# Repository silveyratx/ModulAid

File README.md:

# Modulaid

### Overview
ModulAid was born at UT Austin as a Senior Design Project for 5 Electrical Engineering [students](#contributors). Their senior design class was a special section called "Startup Senior Design" and the students thought up their own project rather than doing an industry or faculty sponsored project.

ModulAid extends a smartphone by providing an easy to use interface for many different types of sensors. The main hub plugs into the smartphone via the headphone jack. Through the connection with the headphone jack, the board is able to communicate with the iOS app as well as harvest power. Sensors can then be attached to the shared sensor board. The board acquires data from the sensors, transmits it to the smartphone, and from there it is displayed to the user.

The team chose to focus on making ModulAid a system for medical devices. The ModulAid app was designed to make access to health information very cheap. The team wanted to make it as easy as possible for people to get insights about their own health and the health in their communities.

### Hardware
Our initial development was done on the NXP Quick-Jack development kit. Then we designed a 2.4 x 1.45 inch PCB, shown below. The Quick-Jack acted as our reference design but with unnecessary components removed and additional components added to satisfy design requirements.

Connecting the board with the phone is as simple as plugging it into the headphone jack. All communication with the phone is done through the four-terminal headphone jack. The four pins in the headphone jack are left audio, right audio, microphone, and ground.

The right audio channel is dedicated to transferring power through a constant audio wave. The signal is fed into a voltage rectifier that converts the low voltage AC signal into a higher voltage DC signal. The DC voltage is fed into a 3.3V regulator that produces a constant voltage for the microcontroller and sensors. The max power that can be harvested from the phone is about 15mW, but the exact value varies from phone to phone. The board also has a CR2032 battery on the back. When additional current is needed for a sensor, it can be drawn from the battery.

Besides providing power to the sensors, the board must be able to communicate with them. We created our own sensor interface so that all our sensors connect through the same port. All our compatible sensors fall into two categories, either those that produce an analog voltage signal or those that communicate through a peripheral on the microcontroller. We added a 2 channel 10-bit ADC (MCP3002) and a dual SPDT (single pole double throw) analog switch (TS3A24157). The signal lines from the sensor port connect to the common inputs of the SPDT switch. The firmware controls the input to the switch to either connect the sensor signals to the ADC or directly to the microcontroller. The schematic is included in the Hardware directory.

### Firmware
The firmware runs on the microcontroller(NXP LPC812) of the ModulAid board. The purpose of the firmware is to create a channel of communication between the smartphone and the various sensors. The firmware receives commands from the smartphone, initializes the hardware, acquires data, and sends the data to the smartphone. Upon reset of the device, the firmware performs the needed initialization for the device, then waits to receive a command from the phone. The command tells the firmware which sensor the user has selected. This is necessary because each sensor communicates with the board differently and requires a unique initialization. For example, the board uses I2C (Inter-Integrated Circuit) to communicate with the IR thermometer, but reads a voltage through the ADC (Analog to Digital Converter) with SPI (Serial Peripheral Interface) for the pulse sensor.

To use the ADC, first we must set the input to the dual SPDT switch such that the sensor wires connect to the inputs of the ADC. We then can sample the ADC by sending a command through SPI to the ADC. The command wakes up the ADC from its sleep state. From there it samples the requested input channel and sends the 10 bit result back. For some sensors, the raw ADC value might be a meaningful piece of data, but in the case of the pulse sensor we must take periodic readings that can be processed into a heart rate in beats per minute (BPM). The pulse sensor readings create a pulse wave. We calculate the BPM by measuring the time between peaks of the waves. The firmware keeps a running average of the BPM and when requested send the value to the smartphone.

For all sensors that don’t make use of the ADC, the input to the dual SPDT switch is set such that the signals from the sensor connect directly to the pins of the microcontroller. The microcontroller, the NXP LPC812, has an internal switch matrix that allows the hardware peripherals to be connected to almost any chosen pin. Because of this switch matrix, we can use the same set of pins for various communication protocols. When the IR thermometer is connected, the firmware assigns the I2C function to the sensor pins. Through the I2C bus, we can poll the thermometer for its most recent temperature reading.

The current hardware revision supports sensors that output an analog voltage or communicate through I2C or UART. SPI could be used for sensor communication if one more signal line was added between the microcontroller and the sensor port.

### iOS Application
The application user interface is the main “face” of the product for a user. Our goal in designing the user interface was to make the application so easy to use that it required no instruction. To accomplish this goal, we decided to use pictures rather than words whenever possible. This way, people of different cultures could use the same version of the app. Screenshots of are included below.

The user interface has three views that carry out the main functions of the application. There is a Home view, a Heatmap view, and a History. The Home view is where the user goes to take a measurement. From the Home view initial screen, the user selects which type of measurement they want to take. After the user selects their device, they are guided by a series of visual prompts to take the reading. In Heatmap view, the user can see what other ModulAid activity is happening around them. The Heatmap shows the locations and relative temperatures of other users. The heatmap is one example of real time health analytics that ModulAid offers, and in the future, it could be used to analyze the health in communities. In History view, a user can see the recent sensor measurements that were taken locally on their personal device.

All collected data is stored anonymously to a FireBase database. Along with the data point we store the location. Further insights and analytics could be generated from this data. The heatmap is one example of this, providing a way to plot the location and severity of fever on a map.

### Demo
Here is a short video demonstrating the functionality: https://vimeo.com/168209562

### Going Forward
Due to the project’s scope in the Senior Design class, ModulAid only supports two sensors, a thermometer, and a heart rate monitor. There are many ways the project could move forward:      
	-Add support for additional sensors     
	-Create user accounts to give more specialized health insights      
	-Create an Android app similiar to the iOS app       
	-Rework the firmware to deal with sensors in a more generic way, allowing new sensors to be added without updating the firmware.    
-and probably many more..

We created this GitHub Repository to document our project and let it live on through the internet. We hope someone out there finds it useful, helpful or even inspiring. Furthermore, the platform is not limited to medical sensors and could be a base for interfacing all sorts of sensors with a smartphone.

### Resources
ModulAid draws from several projects and frameworks:

NXP QuickJack: http://www.nxp.com/products/microcontrollers-and-processors/arm-processors/lpc-cortex-m-mcus/lpc-cortex-m0-plus-m0-mcus/lpc800-low-cost-cortex-m0-plus-mcus/om13069-smartphone-quick-jack-solution:OM13069

LFHeatMap: https://github.com/gpolak/LFHeatMap

Firebase: https://www.firebase.com/

### Contributors
Alex Lee, Cage Johnson, Sam Moser, Alejandro Silveyra, and Ammar Hazim (in order of appearance)    
Photo of team at UT Austin Electrical and Computer Engineering Senior Design Open House - Spring 2016

We would also like to thank our faculty mentor, Ramesh Yerraballi, for his support through out the project.

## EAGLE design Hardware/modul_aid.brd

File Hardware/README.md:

# ModulAid Hardware

Schematic and PCB created in EagleCAD

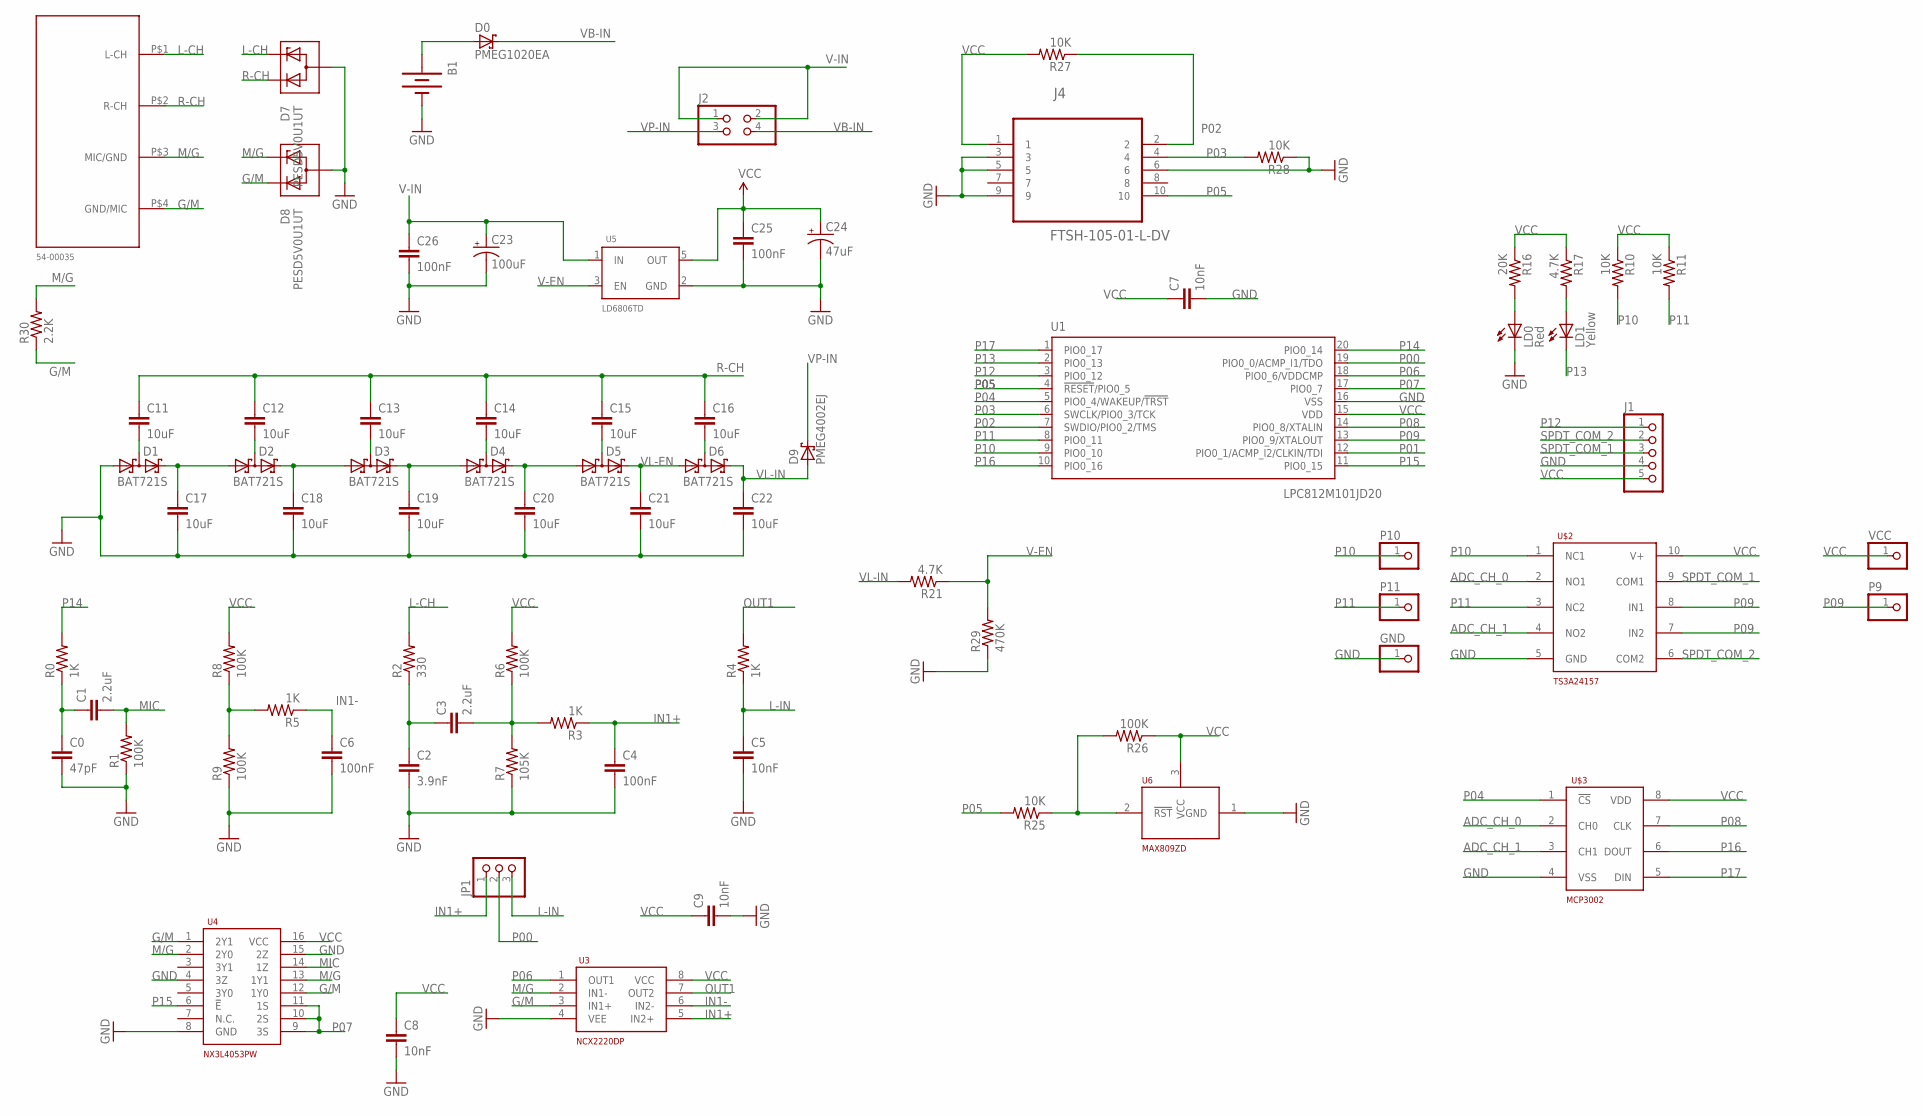
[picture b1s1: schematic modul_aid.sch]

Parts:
B1: BATTERY20PTH; BATTCOM_20MM_PTH
C0: 47pF; 0805-CAP
C1, C3: 2.2uF; 0805-CAP
C2: 3.9nF; 0805-CAP
C4, C6: 100nF; 0805-CAP
C5, C8, C9: 10nF; 0805-CAP
C7: 10nF; 0805
C11, C12, C13, C14, C15, C16, C17, C18, C19, C20, C21, C22: 10uF; 0805-CAP
C23: 100uF; EIA3216-KIT
C24: 47uF; EIA3216-KIT
C25, C26: 100nF; 0805
D0: PMEG1020EA; SOD323(F)
D1, D2, D3, D4, D5, D6: BAT721S; SOT23
D7, D8: PESD5V0U1UT; SOT23
D9: PMEG4002EJ; SOD323(F)
GND: PINHD-1X1; 1X01
J1: PINHD-1X5; 1X05
J2: PINHD-2X2; 2X02
J4: FTSH-105-01-L-DV; SAMTEC_FTSH-105-01-L-DV
JP1: PINHD-1X3; 1X03
LD0: Red; SML0805
LD1: Yellow; SML0805
P9, P10, P11: PINHD-1X1; 1X01
R0, R3, R4, R5: 1K; 0805
R1, R6, R8, R9, R26: 100K; 0805
R2: 330; 0805
R7: 105K; 0805
R10, R11, R25, R27, R28: 10K; 0805
R16: 20K; 0805
R17, R21: 4.7K; 0805
R29: 470K; 0805
R30: 2.2K; 0805
U1: LPC812M101JD20; SOT163-1
U3: NCX2220DP; SOT505-2
U4: NX3L4053PW; S0T403-1
U5: LD6806TD; SOT753
U6: MAX809ZD; SOT23-3
U$2: TS3A24157; VSSOP-10
U$3: MCP3002; SOIC8
U$4: TENSILITY54-00035; EE464SAUDIOJACK
VCC: PINHD-1X1; 1X01

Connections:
ADC_CH_0: U$2.2 (NO1), U$3.2 (CH0)
ADC_CH_1: U$2.4 (NO2), U$3.3 (CH1)
G/M: D8.2 (KD), R30.1, U3.3 (IN1+), U4.1 (2Y1), U4.12 (1Y0), U$4.P$4 (GND/MIC)
GND: B1.2 (-), C0.2, C2.2, C4.2, C5.2, C6.2, C7.2, C8.2, C9.2, C17.2, C18.2, C19.2, C20.2, C21.2, C22.2, C23.C (-), C24.C (-), C25.2, C26.2, D1.1 (A1), D7.3 (CA), D8.3 (CA), GND.1, J1.4, J4.3, J4.5, J4.6, J4.9, LD0.C, R1.1, R7.1, R9.1, R28.1, R29.1, U1.16 (VSS), U3.4 (VEE), U4.4 (3Z), U4.8 (GND), U4.15 (2Z), U5.2 (GND), U6.1 (GND), U$2.5 (GND), U$3.4 (VSS)
IN1+: C4.1, JP1.1, R3.1, U3.5 (IN2+)
IN1-: C6.1, R5.1, U3.6 (IN2-)
L-CH: D7.1 (KESD), R2.2, U$4.P$1 (L-CH)
L-IN: C5.1, JP1.3, R4.1
M/G: D8.1 (KESD), R30.2, U3.2 (IN1-), U4.2 (2Y0), U4.13 (1Y1), U$4.P$3 (MIC/GND)
MIC: C1.2, R1.2, U4.14 (1Z)
unnamed: C11.2, D1.3 (K1A2)
unnamed: C12.2, D2.3 (K1A2)
unnamed: C13.2, D3.3 (K1A2)
unnamed: C14.2, D4.3 (K1A2)
unnamed: C15.2, D5.3 (K1A2)
unnamed: C16.2, D6.3 (K1A2)
unnamed: B1.1 (+), D0.2 (A)
unnamed: C0.1, C1.1, R0.1
unnamed: C17.1, D1.2 (K2), D2.1 (A1)
unnamed: C18.1, D2.2 (K2), D3.1 (A1)
unnamed: C19.1, D3.2 (K2), D4.1 (A1)
unnamed: C20.1, D4.2 (K2), D5.1 (A1)
unnamed: R5.2, R8.1, R9.2
unnamed: C2.1, C3.1, R2.1
unnamed: R25.1, R26.2, U6.2 (!RST)
unnamed: C3.2, R3.2, R6.1, R7.2
unnamed: LD0.A, R16.2
unnamed: LD1.A, R17.2
OUT1: R4.2, U3.7 (OUT2)
P00: JP1.2, U1.19 (PIO0_0/ACMP_I1/TDO)
P01: U1.12 (PIO0_1/ACMP_I2/CLKIN/TDI)
P02: J4.2, R27.1, U1.7 (SWDIO/PIO0_2/TMS)
P03: J4.4, R28.2, U1.6 (SWCLK/PIO0_3/TCK)
P04: U1.5 (PIO0_4/WAKEUP/!TRST!), U$3.1 (!CS)
P05: J4.10, R25.2, U1.4 (!RESET!/PIO0_5)
P06: U1.18 (PIO0_6/VDDCMP), U3.1 (OUT1)
P07: U1.17 (PIO0_7), U4.9 (3S), U4.10 (2S), U4.11 (1S)
P08: U1.14 (PIO0_8/XTALIN), U$3.7 (CLK)
P09: P9.1, U1.13 (PIO0_9/XTALOUT), U$2.7 (IN2), U$2.8 (IN1)
P10: P10.1, R10.2, U1.9 (PIO0_10), U$2.1 (NC1)
P11: P11.1, R11.2, U1.8 (PIO0_11), U$2.3 (NC2)
P12: J1.1, U1.3 (PIO0_12)
P13: LD1.C, U1.2 (PIO0_13)
P14: R0.2, U1.20 (PIO0_14)
P15: U1.11 (PIO0_15), U4.6 (!E)
P16: U1.10 (PIO0_16), U$3.6 (DOUT)
P17: U1.1 (PIO0_17), U$3.5 (DIN)
R-CH: C11.1, C12.1, C13.1, C14.1, C15.1, C16.1, D7.2 (KD), U$4.P$2 (R-CH)
SPDT_COM_1: J1.3, U$2.9 (COM1)
SPDT_COM_2: J1.2, U$2.6 (COM2)
V-EN: R21.1, R29.2, U5.3 (EN)
V-IN: C23.A (+), C26.1, J2.1, J2.2, U5.1 (IN)
VB-IN: D0.1 (K), J2.4
VCC: C7.1, C8.1, C9.1, C24.A (+), C25.1, J1.5, J4.1, R6.2, R8.2, R10.1, R11.1, R16.1, R17.1, R26.1, R27.2, U1.15 (VDD), U3.8 (VCC), U4.16 (VCC), U5.5 (OUT), U6.3 (VCC), U$2.10 (V+), U$3.8 (VDD), VCC.1
VL-EN: C21.1, D5.2 (K2), D6.1 (A1)
VL-IN: C22.1, D6.2 (K2), D9.2 (A), R21.2
VP-IN: D9.1 (K), J2.3

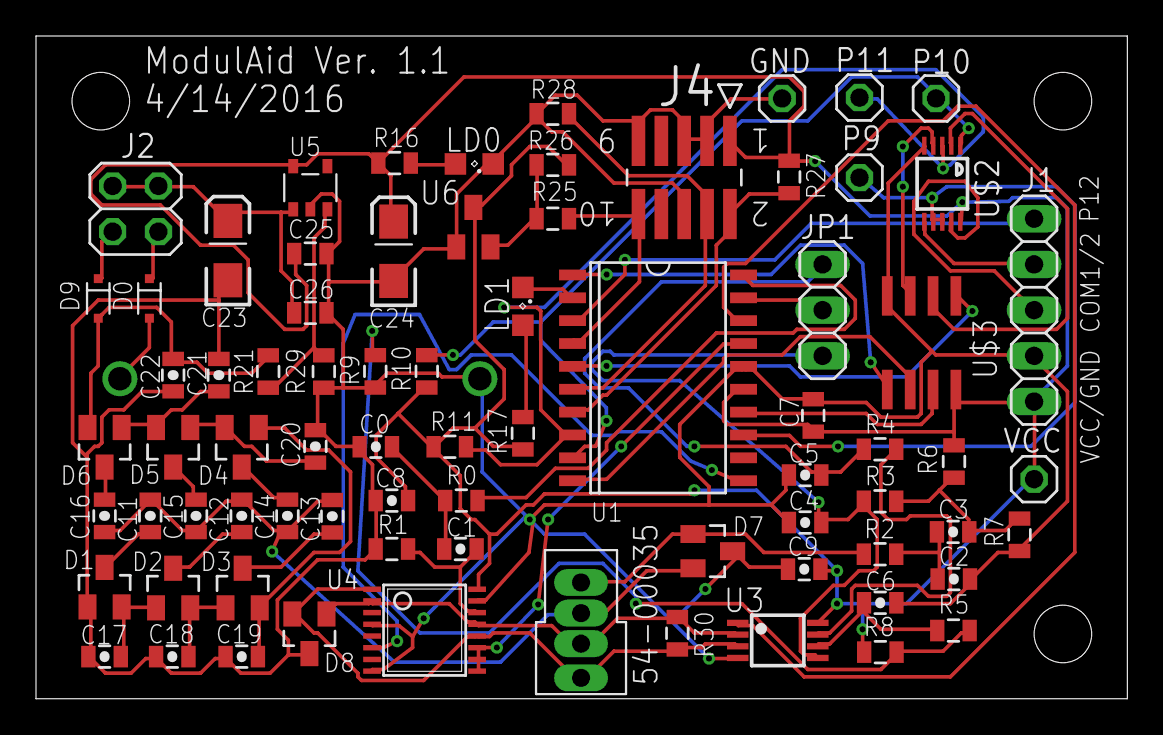
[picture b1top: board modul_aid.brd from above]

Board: 2 copper layers, 60.6 x 36.8 mm, 77 parts (1 on the bottom side), 56 nets.

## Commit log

2016-05-16 adds folders
2016-05-16 transfer to github
2016-05-16 syntax fixes
2016-05-16 line spacing fix
2016-05-16 adds images
2016-05-16 readme test
2016-05-17 iOS application
2016-05-17 cleared readme
2016-05-17 added schematic and pcb files
2016-05-17 adds ios images
2016-05-17 fix to images
2016-05-17 fix to image path
2016-05-17 iOS application, fixed ModulAid folder issue
2016-05-17 fixed iOS project after changing folder name from ModulAid to modulaidUI
2016-05-17 added readme for iOS app
2016-05-17 fixed iOS readme
2016-05-17 readme update
2016-05-17 path fix
2016-05-17 style fix
2016-05-17 photo description
2016-05-17 team name ordering change
2016-05-21 readme addiitions
2016-05-21 added heatmap screenshot
2016-05-21 smaller heatmap screenshot
2016-05-21 screenshot replaced with combo of all three screens
2016-05-21 copy fixes
2016-05-21 added hardware and firmware sections
2016-05-21 created an iOS section
2016-05-21 fixed paths to pcb images
2016-05-21 pcb combo photo added
2016-05-21 rel link to section
2016-05-21 fixed link
2016-05-21 and maybe now the link will work
2016-05-21 moved pcb photo
2016-05-21 added info to iOS section
2016-05-21 added going forward section
2016-05-21 line spacing fixes
2016-05-21 edits for clarity
2016-05-26 adds link to vimeo

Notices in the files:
parts and their libraries:
SparkFun-Electromechanical: Licensing: Creative Commons ShareAlike 4.0 International - https://creativecommons.org/licenses/by-sa/4.0
